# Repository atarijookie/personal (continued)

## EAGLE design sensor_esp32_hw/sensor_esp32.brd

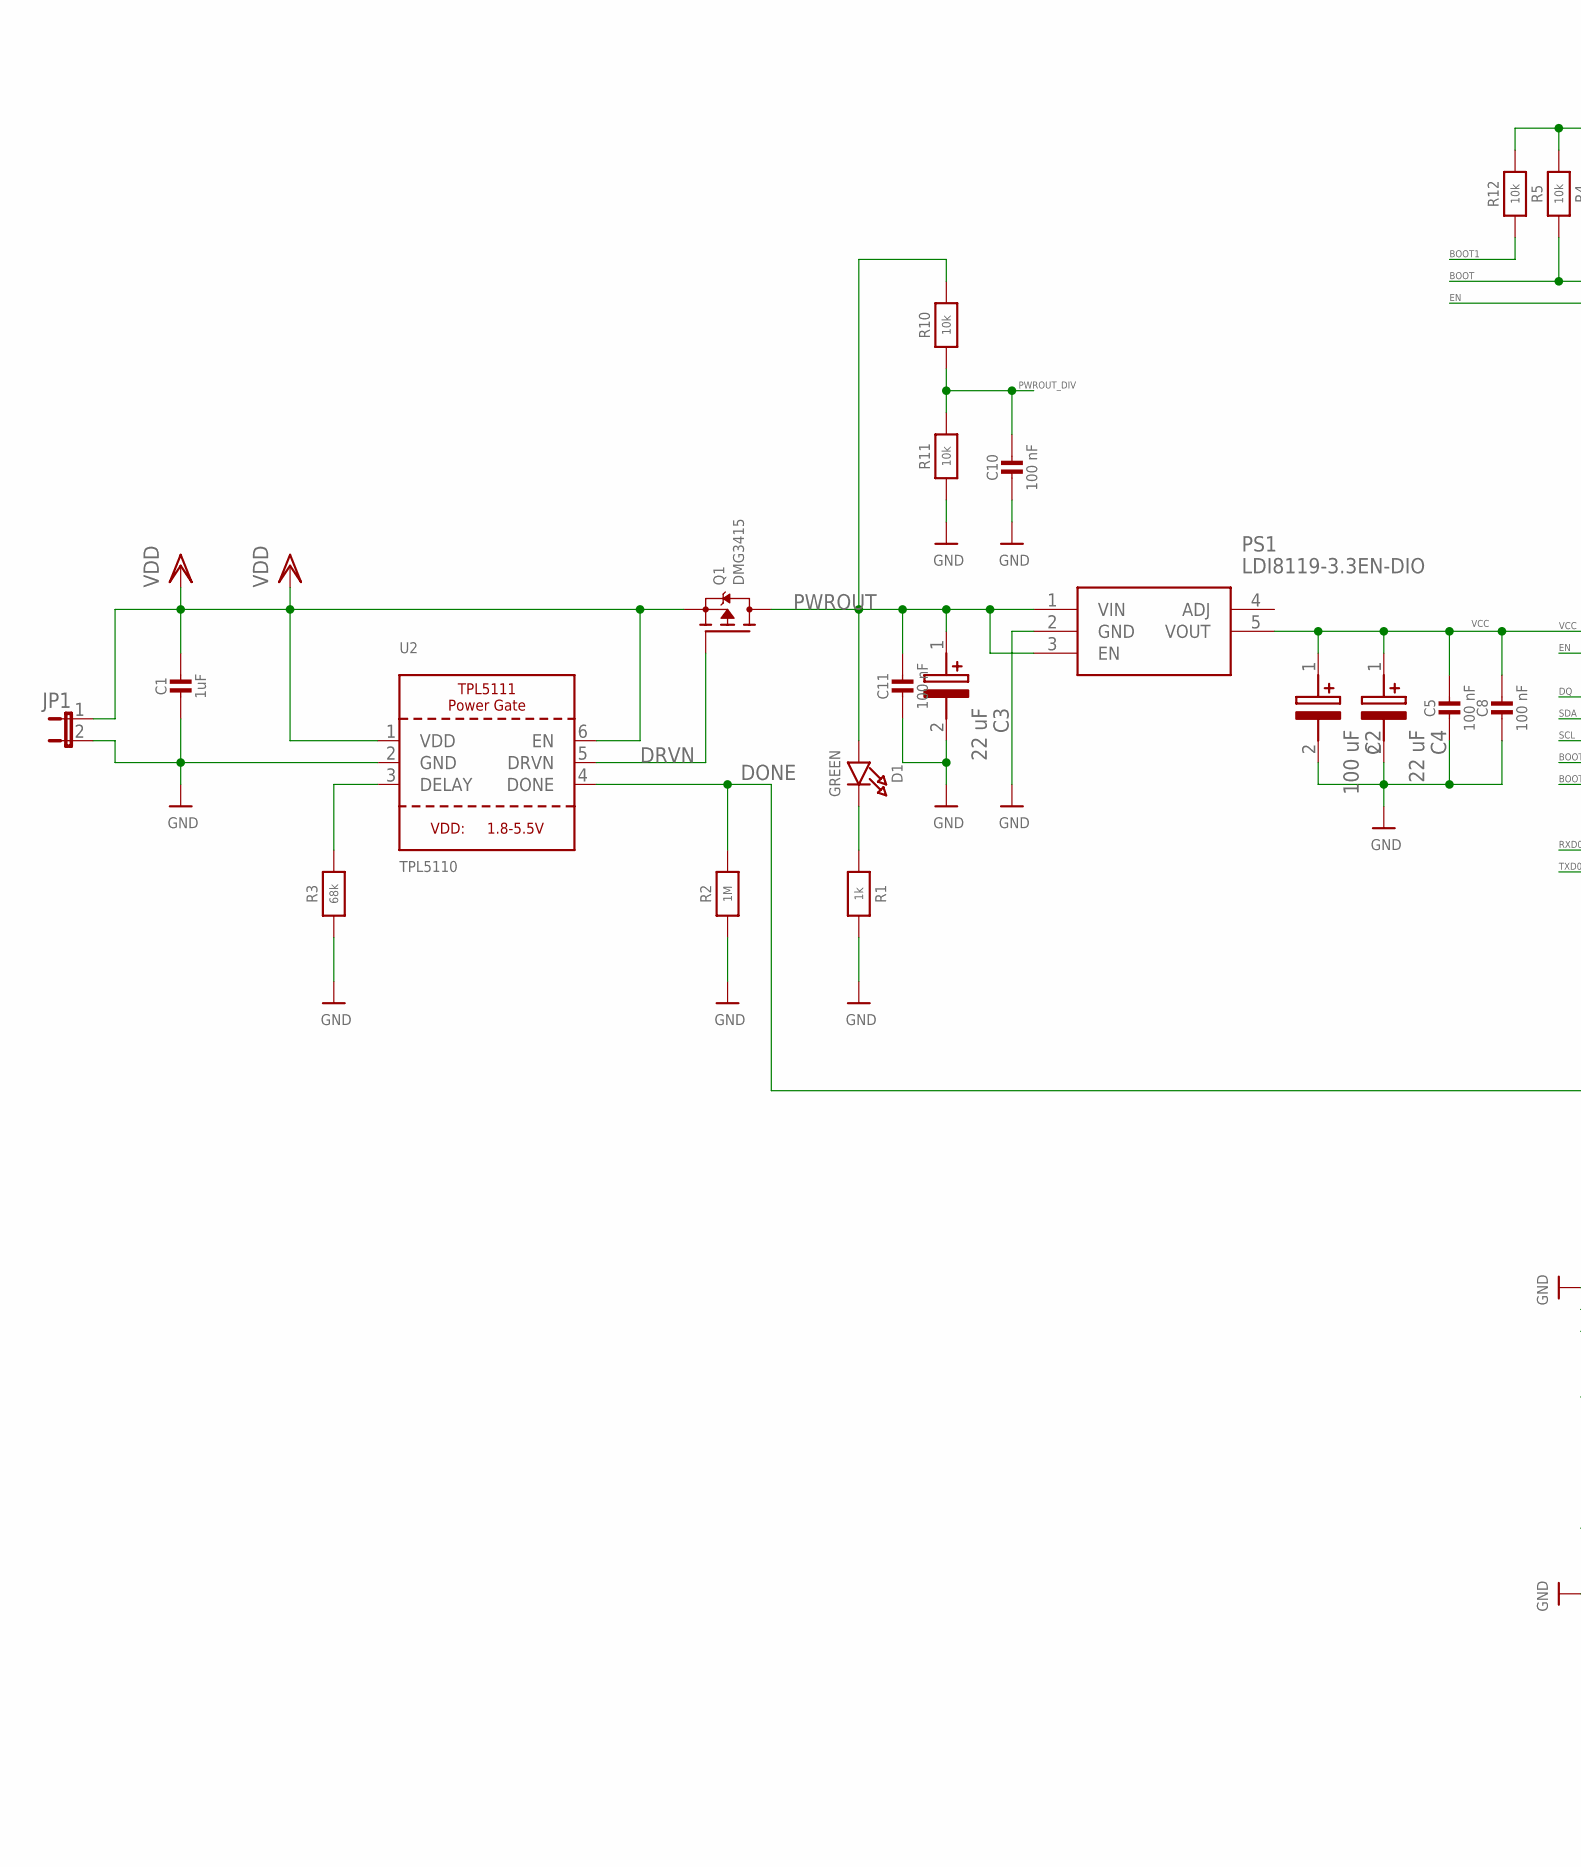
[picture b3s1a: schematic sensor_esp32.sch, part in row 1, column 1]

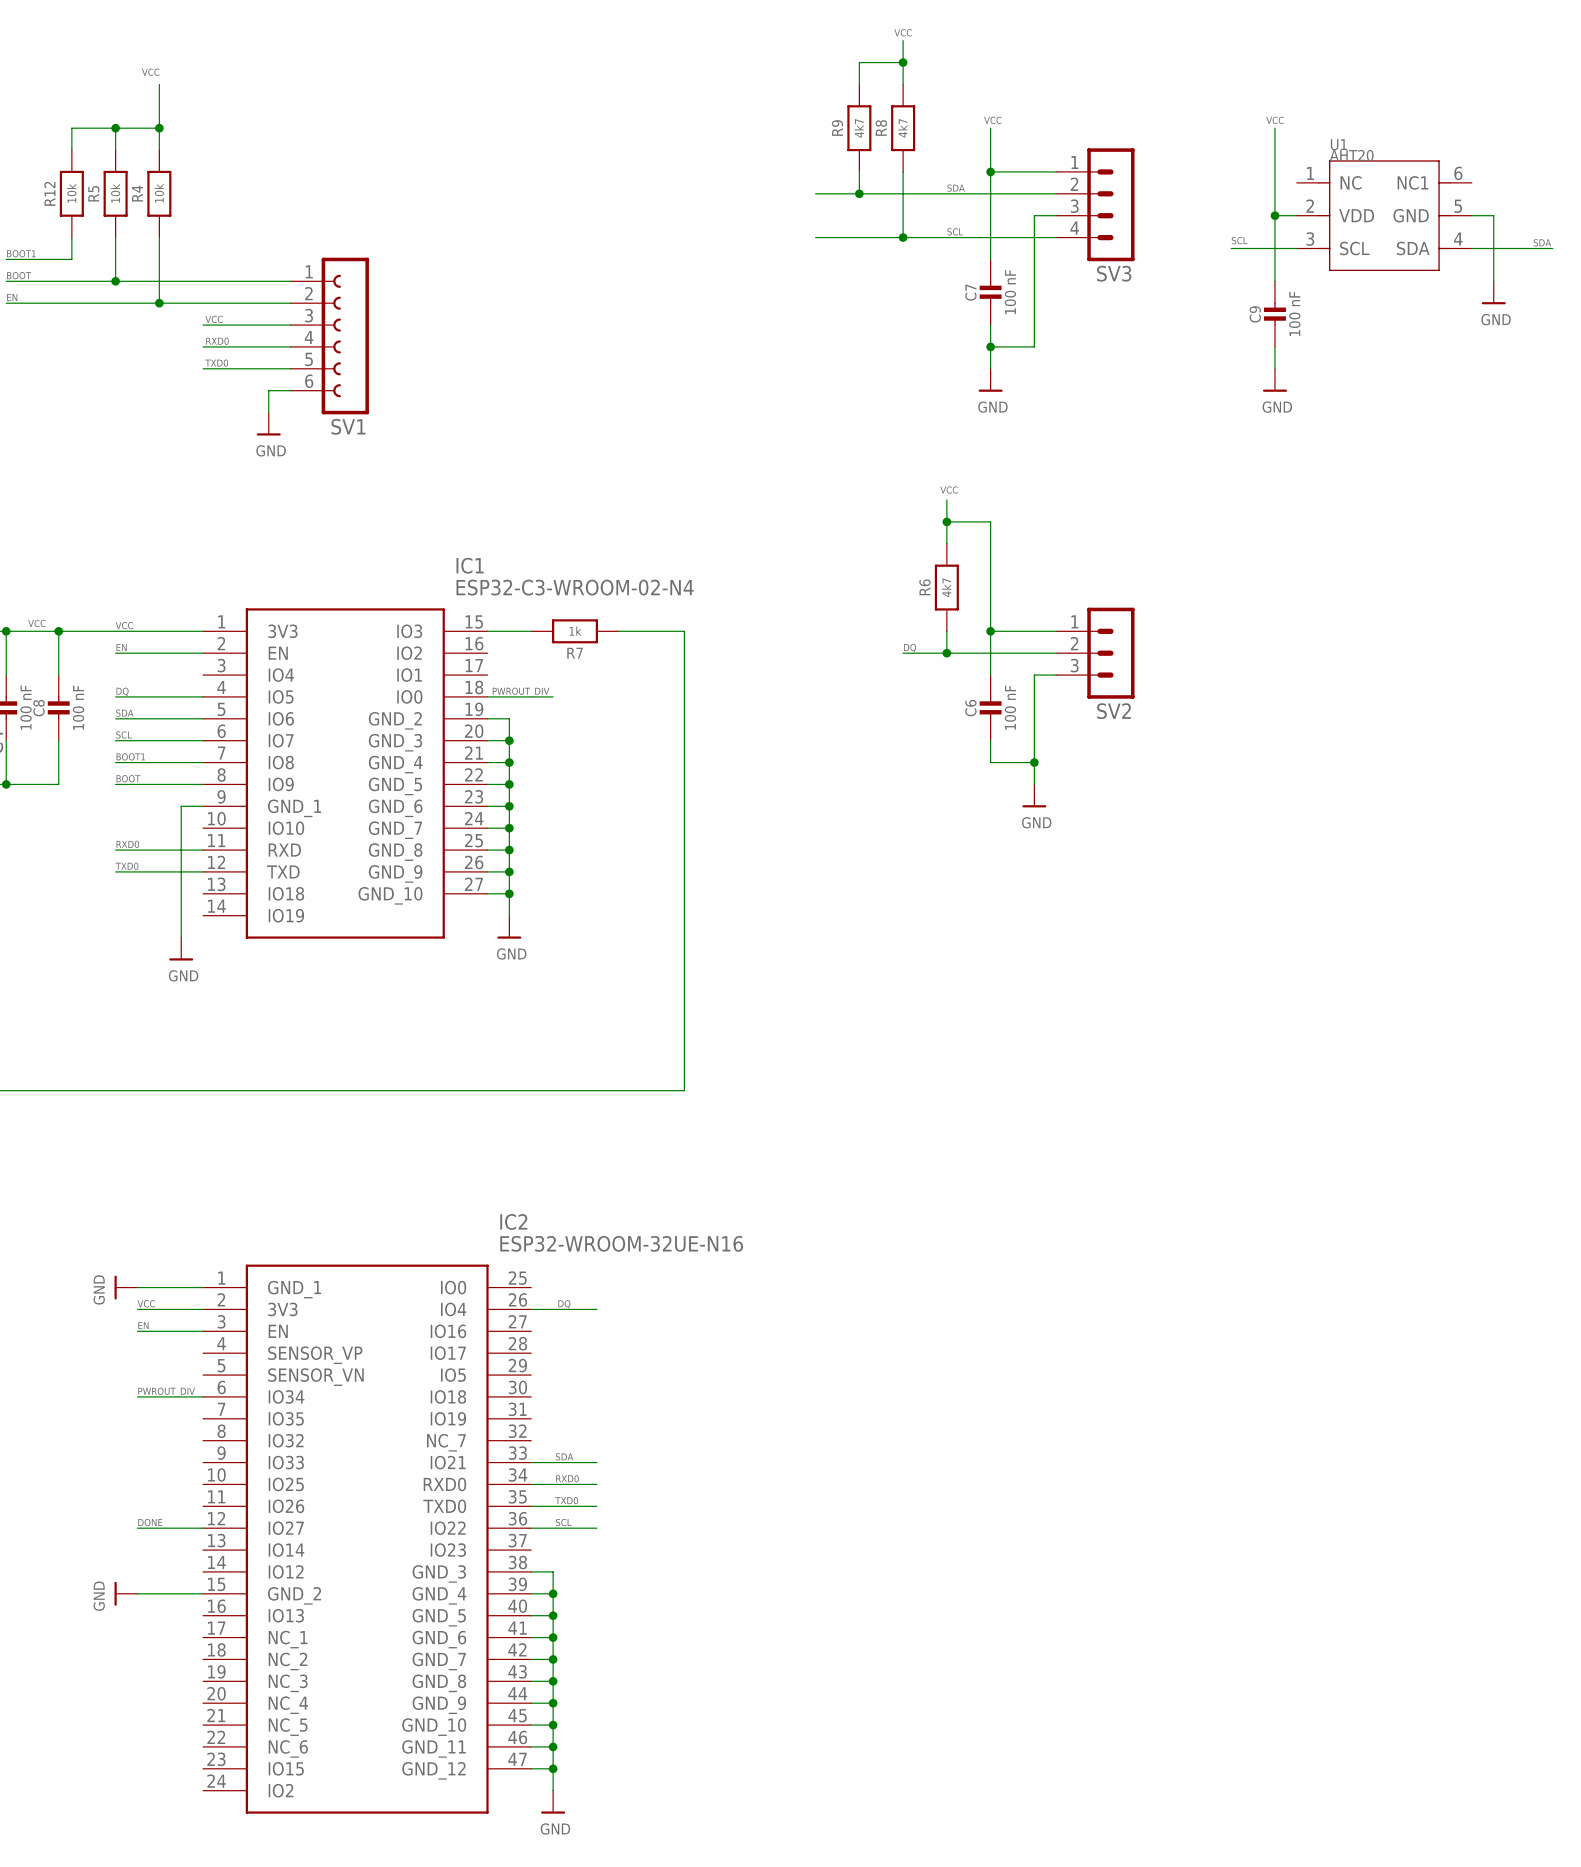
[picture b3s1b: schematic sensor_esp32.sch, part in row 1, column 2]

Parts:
C1: 1uF; 0805-NO
C2: 100 uF; CAPPM6032X280N
C3, C4: 22 uF; CAPPM3216X180N; MANUFACTURER_PART_NUMBER 293D226X9010A2TE3
C5, C6, C7, C8, C9, C10, C11: 100 nF; _0603
D1: GREEN; CHIPLED_0805_NOOUTLINE
IC1: ESP32-C3-WROOM-02-N4; ESP32C3WROOM02N4
IC2: ESP32-WROOM-32UE-N16; ESP32WROOM32UEN16
JP1: JP1E; JP1
PS1: LDI8119-3.3EN-DIO; SOT95P282X145-5N
Q1: DMG3415; SOT23-WIDE
R1, R7: 1k; _0603
R2: 1M; _0603
R3: 68k; _0603
R4, R5, R10, R11, R12: 10k; _0603
R6, R8, R9: 4k7; _0603
SV1: FE06-1; FE06
SV2: MA03-1
SV3: MA04-1
U1: AHT20; SNR6-1.0-3X3X1MM
U2: TPL5110; SOT23-6

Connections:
BOOT: IC1.8 (IO9), R5.1, SV1.1
BOOT1: IC1.7 (IO8), R12.1
DELAY: R3.2, U2.3 (DELAY)
DONE: IC2.12 (IO27), R2.2, R7.1, U2.4 (DONE)
DQ: IC1.4 (IO5), IC2.26 (IO4), R6.1, SV2.2
DRVN: Q1.1 (G), U2.5 (DRVN)
EN: IC1.2 (EN), IC2.3 (EN), R4.1, SV1.2
GND: C1.2, C2.2 (-), C3.2 (-), C4.2 (-), C5.2, C6.2, C7.2, C8.2, C9.2, C10.2, C11.2, IC1.9 (GND_1), IC1.19 (GND_2), IC1.20 (GND_3), IC1.21 (GND_4), IC1.22 (GND_5), IC1.23 (GND_6), IC1.24 (GND_7), IC1.25 (GND_8), IC1.26 (GND_9), IC1.27 (GND_10), IC2.1 (GND_1), IC2.15 (GND_2), IC2.38 (GND_3), IC2.39 (GND_4), IC2.40 (GND_5), IC2.41 (GND_6), IC2.42 (GND_7), IC2.43 (GND_8), IC2.44 (GND_9), IC2.45 (GND_10), IC2.46 (GND_11), IC2.47 (GND_12), JP1.2, PS1.2 (GND), R1.2, R2.1, R3.1, R11.1, SV1.6, SV2.3, SV3.3, U1.5 (GND), U2.2 (GND)
unnamed: IC1.15 (IO3), R7.2
unnamed: D1.C, R1.1
PWROUT: C3.1 (+), C11.1, D1.A, PS1.1 (VIN), PS1.3 (EN), Q1.3 (D), R10.2
PWROUT_DIV: C10.1, IC1.18 (IO0), IC2.6 (IO34), R10.1, R11.2
RXD0: IC1.11 (RXD), IC2.34 (RXD0), SV1.4
SCL: IC1.6 (IO7), IC2.36 (IO22), R8.1, SV3.4, U1.3 (SCL)
SDA: IC1.5 (IO6), IC2.33 (IO21), R9.1, SV3.2, U1.4 (SDA)
TXD0: IC1.12 (TXD), IC2.35 (TXD0), SV1.5
VCC: C2.1 (+), C4.1 (+), C5.1, C6.1, C7.1, C8.1, C9.1, IC1.1 (3V3), IC2.2 (3V3), PS1.5 (VOUT), R4.2, R5.2, R6.2, R8.2, R9.2, R12.2, SV1.3, SV2.1, SV3.1, U1.2 (VDD)
VDD: C1.1, JP1.1, Q1.2 (S), U2.1 (VDD), U2.6 (EN)

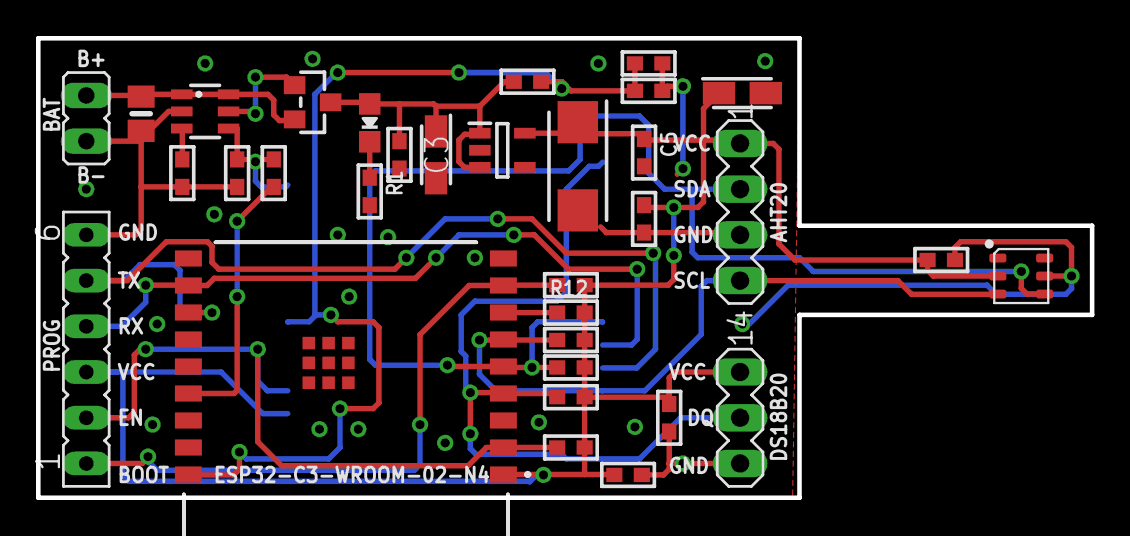
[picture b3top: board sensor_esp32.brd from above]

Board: 2 copper layers, 58.5 x 25.5 mm, 34 parts (1 on the bottom side), 18 nets.

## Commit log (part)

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2026-03-18 added db and tables creation, receiving data from sensors, storing to db, aggregation
2026-03-18 added esp8266 temp sensor
2026-03-18 daily, monthly, yearly graph added
2026-03-19 added hw for esp32 sensor with tpl5110 and aht20
2026-03-19 added another esp32 with u.fl connection (if needed)
2026-03-19 minor routing improvements
2026-03-20 added esp-now to wifi bridge
2026-03-20 modified esp8266 sensor to use esp-now
2026-03-20 modified temp sensor for esp32
2026-03-20 minor improvements before fabrication
2026-04-01 added battery level to db and into ingest
2026-04-02 fixes to esp8266 sensor code
2026-04-03 fixes to schematic and pcb, also made esp32 sensor work
2026-04-05 better showing of temperature and humidity, added battery view
2026-04-07 added notifications to ntfy, graphs now more curly, month graph shows also min and max
2026-04-09 added pull up on BOOT1 for flashing via serial
2026-04-09 graph lines back to just from point to point instead of bezier curves
2026-04-10 all sensors now show in graphs by default. added db backup scripts
2026-04-12 improvements to temperature graphs
